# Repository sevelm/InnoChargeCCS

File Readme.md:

<!-- List of references -->
## Project References

### PyPLC
raspberry Pi based EVSE Controller https://github.com/uhi22/pyPLC

### EVerest
CPP Implementation of message structure https://github.com/EVerest/libiso15118
List of open charging management Repo https://github.com/EVerest

### SmartEVSE
Most promising software solution to read car SOC https://github.com/SmartEVSE/ESP32-PLC

### uhi22
Link of many ccs related project https://github.com/uhi22

### FOCCCI
Main reference for scheatic and hardware designs of QCA7005 https://github.com/uhi22/foccci

## Alternative Chips
`IS32CG5317` Seems an alternative for QCA7000

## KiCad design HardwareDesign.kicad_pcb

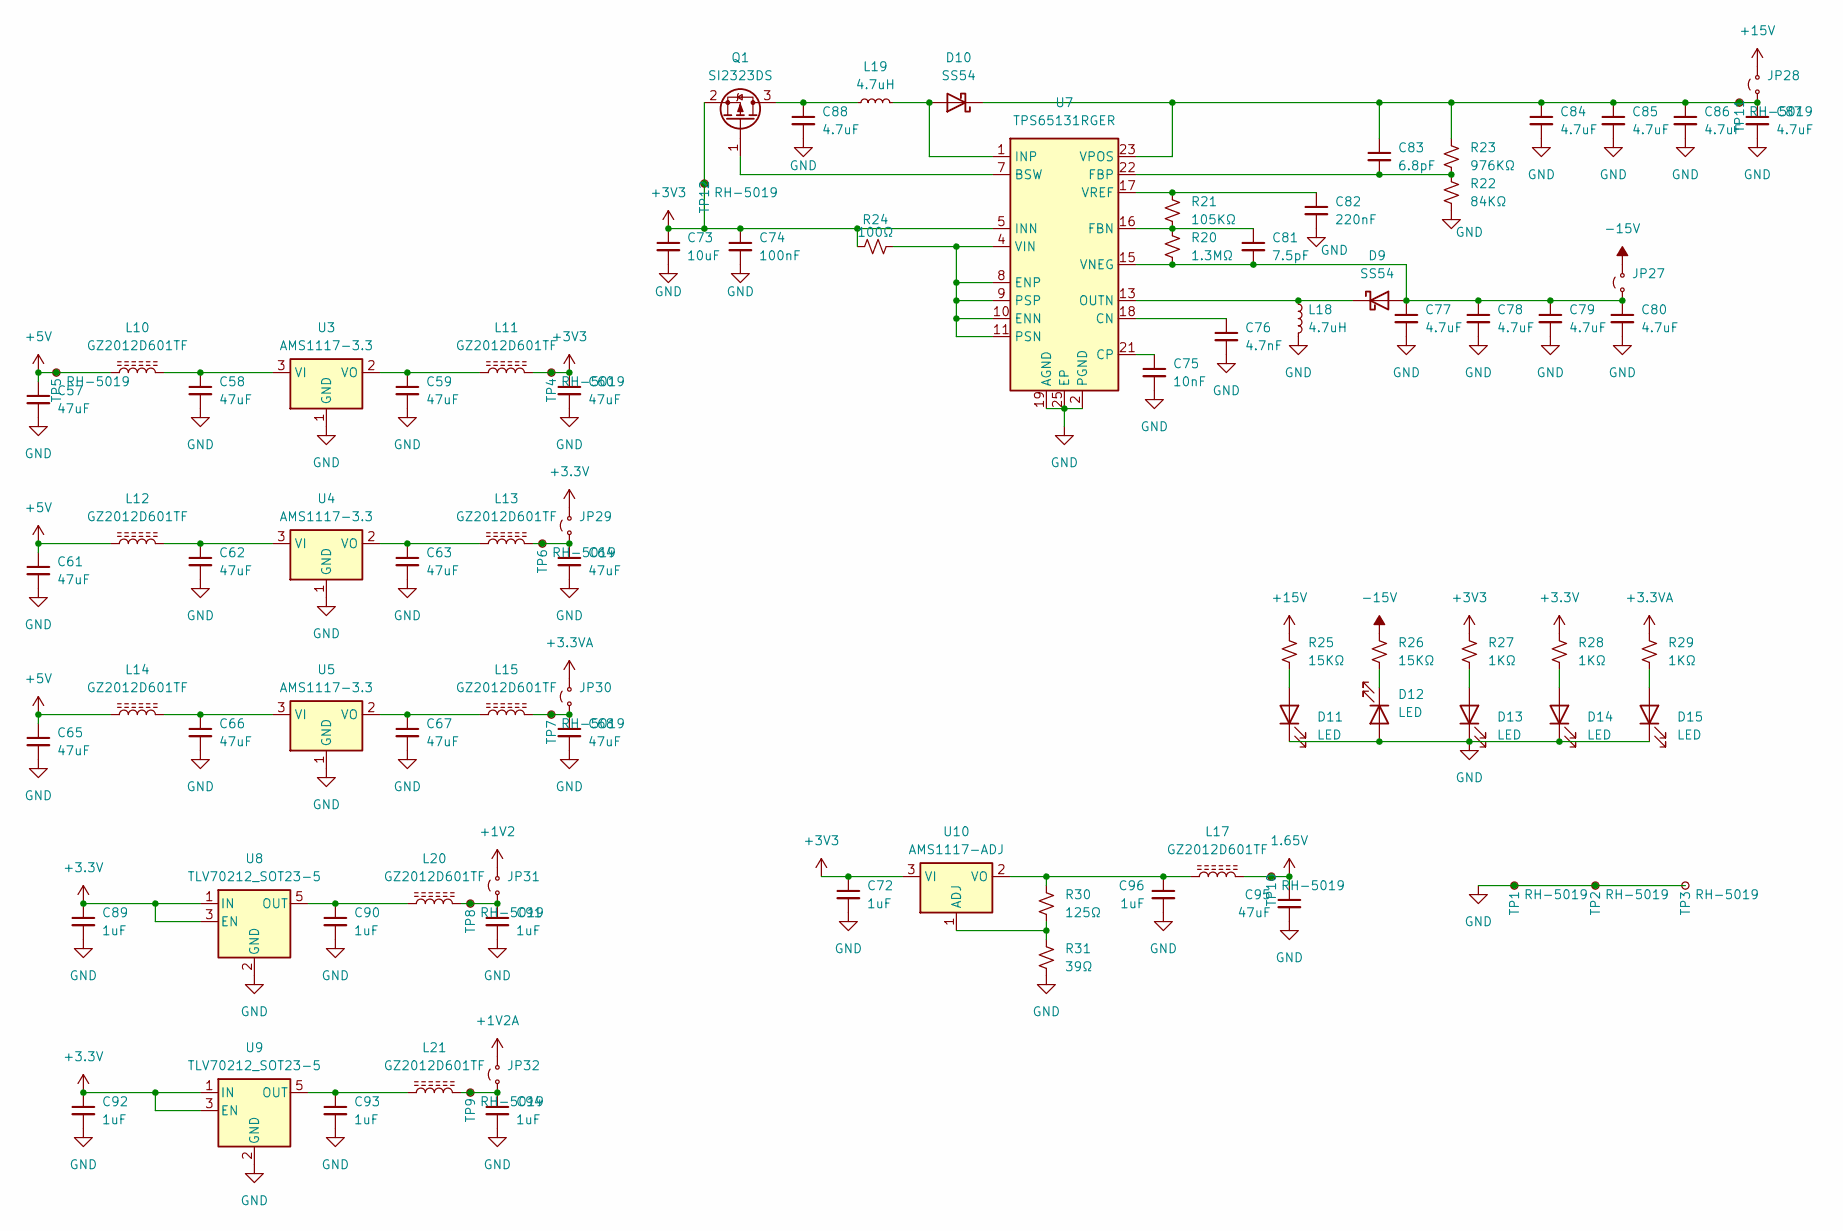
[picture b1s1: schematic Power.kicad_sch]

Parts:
C57, C58, C59, C60, C61, C62, C63, C64, C65, C66, C67, C68, C95: 47uF; C_0805_2012Metric; JLCPCB Part No # C16780
C72, C89, C90, C91, C92, C93, C94, C96: 1uF; C_0805_2012Metric; JLCPCB Part No # C28323
C73: 10uF; C_0805_2012Metric; JLCPCB Part No # C440198
C74: 100nF; C_0805_2012Metric; JLCPCB Part No # C28233
C75: 10nF; C_0805_2012Metric; JLCPCB Part No # C1710
C76: 4.7nF; C_0805_2012Metric; JLCPCB Part No # C1744
C77, C78, C79, C80, C84, C85, C86, C87, C88: 4.7uF; C_0805_2012Metric; JLCPCB Part No # C1779
C81: 7.5pF; C_0805_2012Metric; JLCPCB Part No # C519943
C82: 220nF; C_0805_2012Metric; JLCPCB Part No # C5378
C83: 6.8pF; C_0805_2012Metric; JLCPCB Part No # C1832
D9, D10: SS54; D_SMA; JLCPCB Part No # C7420369
D11, D12, D13, D14, D15: LED; LED_0805_2012Metric; JLCPCB Part No # C2297
JP27, JP28, JP29, JP30, JP31, JP32: SolderJumper-2_P1.3mm_Open_RoundedPad1.0x1.5mm
L10, L11, L12, L13, L14, L15, L17, L20, L21: GZ2012D601TF; L_0805_2012Metric; JLCPCB Part No # C1017
L18, L19: 4.7uH; L_Sunlord_SWPA3015S; JLCPCB Part No # C19398
Q1: SI2323DS; SOT-23-3; JLCPCB Part No # C5182044
R20: 1.3MΩ; R_0805_2012Metric; JLCPCB Part No # C413341
R21: 105KΩ; R_0805_2012Metric; JLCPCB Part No # C17410
R22: 84KΩ; R_0603_1608Metric; JLCPCB Part No # C706010
R23: 976KΩ; R_0805_2012Metric; JLCPCB Part No # C218737
R24: 100Ω; R_0805_2012Metric; JLCPCB Part No # C17408
R25, R26: 15KΩ; R_0805_2012Metric; JLCPCB Part No # C17475
R27, R28, R29: 1KΩ; R_0805_2012Metric; JLCPCB Part No # C17513
R30: 125Ω; R_0805_2012Metric; JLCPCB Part No # C3020059
R31: 39Ω; R_0805_2012Metric; JLCPCB Part No # C137534
TP1, TP2, TP3, TP4, TP5, TP6, TP7, TP8, TP9, TP10, TP11, TP12: RH-5019; TestPoint_Keystone_5019_Minature; JLCPCB Part No # C5199800
U3, U4, U5: AMS1117-3.3; SOT-223-3_TabPin2; JLCPCB Part No # C6186
U7: TPS65131RGER; VQFN-24-1EP_4x4mm_P0.5mm_EP2.45x2.45mm_ThermalVias; JLCPCB Part No # C87663
U8, U9: TLV70212_SOT23-5; SOT-23-5; JLCPCB Part No # C81462
U10: AMS1117-ADJ; SOT-223-3_TabPin2; JLCPCB Part No # C347224

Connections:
1.65V: C95.1, L17.1, TP10.1; also elsewhere on the board
+1V2: JP31.2 (B); also elsewhere on the board
+1V2A: JP32.2 (B); also elsewhere on the board
+3.3V: C89.1, C92.1, JP29.2 (B), R28.1, U8.1 (IN), U8.3 (EN), U9.1 (IN), U9.3 (EN); also elsewhere on the board
+3.3VA: JP30.2 (B), R29.1; also elsewhere on the board
+3V3: C60.1, C72.1, C73.1, C74.1, L11.2, Q1.2 (S), R24.1, R27.1, TP4.1, TP12.1, U7.5 (INN), U7.6 (INN), U10.3 (VI); also elsewhere on the board
+5V: C57.1, C61.1, C65.1, L10.1, L12.1, L14.1, TP5.1; also elsewhere on the board
+15V: JP28.2 (B), R25.1; also elsewhere on the board
-15V: JP27.2 (B), R26.1; also elsewhere on the board
GND: C57.2, C58.2, C59.2, C60.2, C61.2, C62.2, C63.2, C64.2, C65.2, C66.2, C67.2, C68.2, C72.2, C73.2, C74.2, C75.2, C76.2, C77.2, C78.2, C79.2, C80.2, C82.2, C84.2, C85.2, C86.2, C87.2, C88.2, C89.2, C90.2, C91.2, C92.2, C93.2, C94.2, C95.2, C96.2, D11.1 (K), D12.2 (A), D13.1 (K), D14.1 (K), D15.1 (K), L18.2, R22.2, R31.2, TP1.1, TP2.1, TP3.1, U3.1 (GND), U4.1 (GND), U5.1 (GND), U7.2 (PGND), U7.3 (PGND), U7.19 (AGND), U7.25 (EP), U8.2 (GND), U9.2 (GND); also elsewhere on the board
unnamed: C77.1, C78.1, C79.1, C80.1, C81.2, D9.2 (A), JP27.1 (A), R20.2, U7.15 (VNEG)
unnamed: D9.1 (K), L18.1, U7.13 (OUTN), U7.14 (OUTN)
unnamed: D10.2 (A), L19.2, U7.1 (INP), U7.24 (INP)
unnamed: C83.1, C84.1, C85.1, C86.1, C87.1, D10.1 (K), JP28.1 (A), R23.1, TP11.1, U7.23 (VPOS)
unnamed: D11.2 (A), R25.2
unnamed: D12.1 (K), R26.2
unnamed: D13.2 (A), R27.2
unnamed: D14.2 (A), R28.2
unnamed: D15.2 (A), R29.2
unnamed: C64.1, JP29.1 (A), L13.2, TP6.1
unnamed: C68.1, JP30.1 (A), L15.2, TP7.1
unnamed: C91.1, JP31.1 (A), L20.2, TP8.1
unnamed: C94.1, JP32.1 (A), L21.2, TP9.1
unnamed: C88.1, L19.1, Q1.3 (D)
unnamed: Q1.1 (G), U7.7 (BSW)
unnamed: C58.1, L10.2, U3.3 (VI)
unnamed: C59.1, L11.1, U3.2 (VO)
unnamed: C62.1, L12.2, U4.3 (VI)
unnamed: C63.1, L13.1, U4.2 (VO)
unnamed: C66.1, L14.2, U5.3 (VI)
unnamed: C67.1, L15.1, U5.2 (VO)
unnamed: C76.1, U7.18 (CN)
unnamed: C75.1, U7.21 (CP)
unnamed: R24.2, U7.4 (VIN), U7.8 (ENP), U7.9 (PSP), U7.10 (ENN), U7.11 (PSN)
unnamed: C81.1, R20.1, R21.2, U7.16 (FBN)
unnamed: C83.2, R22.1, R23.2, U7.22 (FBP)
unnamed: C82.1, R21.1, U7.17 (VREF)
unnamed: C90.1, L20.1, U8.5 (OUT)
unnamed: C93.1, L21.1, U9.5 (OUT)
unnamed: R30.2, R31.1, U10.1 (ADJ)
unnamed: C96.1, L17.2, R30.1, U10.2 (VO)

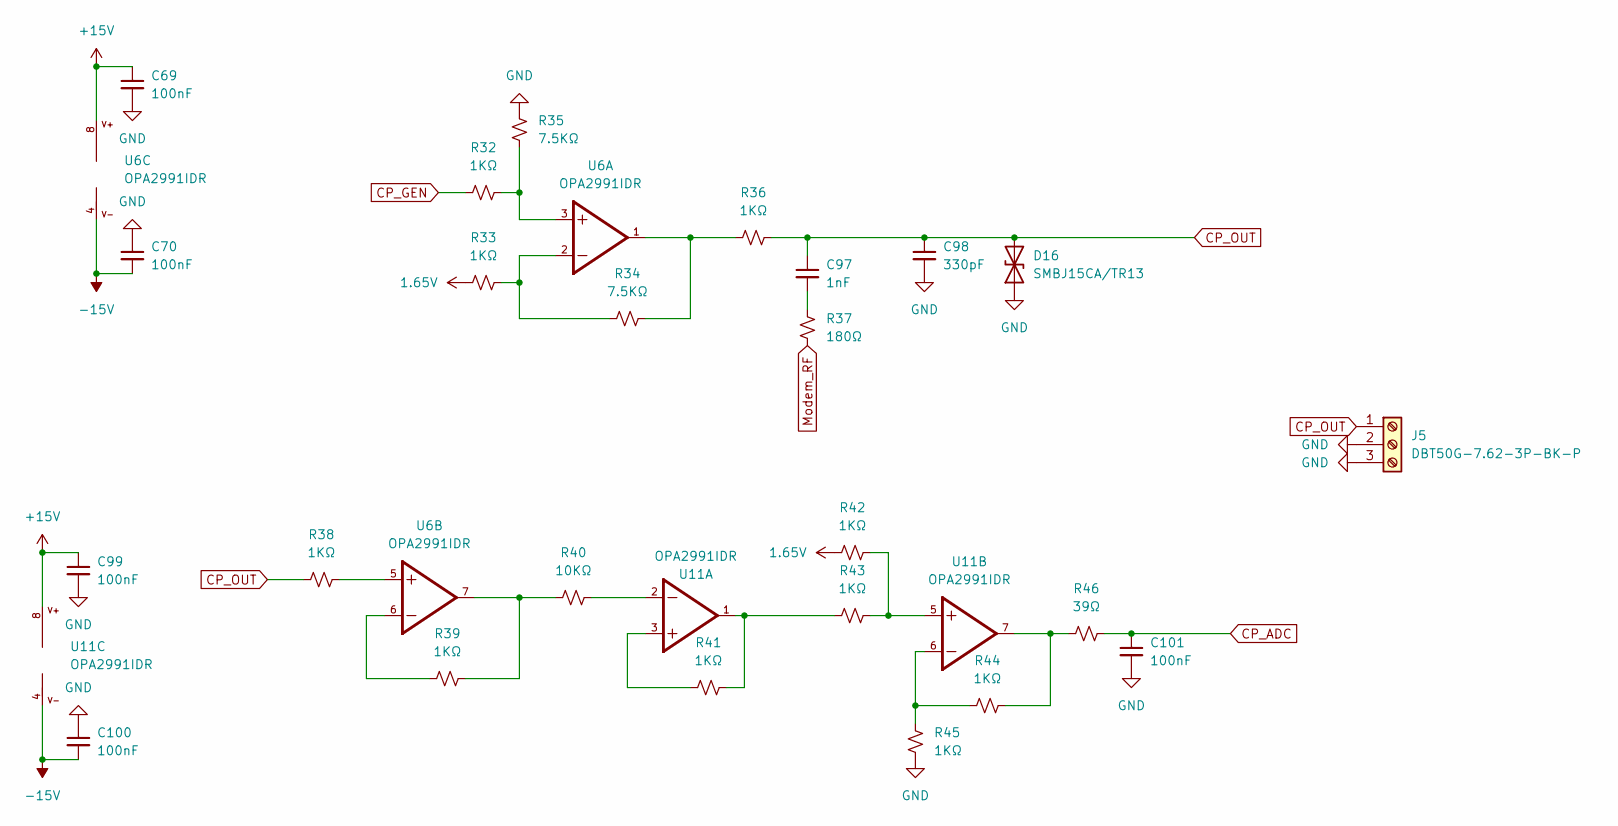
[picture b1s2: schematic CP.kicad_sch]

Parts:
C69, C70, C99, C100, C101: 100nF; C_0805_2012Metric; JLCPCB Part No # C28233
C97: 1nF; C_0805_2012Metric; JLCPCB Part No # C46653
C98: 330pF; C_0805_2012Metric; JLCPCB Part No # C1815
D16: SMBJ15CA/TR13; D_SMB; JLCPCB Part No # C78410
J5: DBT50G-7.62-3P-BK-P; PhoenixContact_GMSTBVA_2,5_3-G-7,62_1x03_P7.62mm_Vertical; JLCPCB Part No # C496128
R32, R33, R36, R38, R39, R41, R42, R43, R44, R45: 1KΩ; R_0805_2012Metric; JLCPCB Part No # C17513
R34, R35: 7.5KΩ; R_0805_2012Metric; JLCPCB Part No # C17807
R37: 180Ω; R_0805_2012Metric; JLCPCB Part No # C25270
R40: 10KΩ; R_0805_2012Metric; JLCPCB Part No # C17414
R46: 39Ω; R_0805_2012Metric; JLCPCB Part No # C137534
U6, U11: OPA2991IDR; SOIC-8_3.9x4.9mm_P1.27mm; MOUSER_PART_NUMBER 595-OPA2991IPWR

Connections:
1.65V: R33.2, R42.2; also elsewhere on the board
+15V: C69.1, C99.1, U6.8, U11.8; also elsewhere on the board
-15V: C70.2, C100.2, U6.4, U11.4; also elsewhere on the board
CP_ADC: C101.1, R46.1; also elsewhere on the board
CP_GEN: R32.1; also elsewhere on the board
CP_OUT: C97.1, C98.1, D16.2 (A2), J5.1, R36.1, R38.2
GND: C69.2, C70.1, C98.2, C99.2, C100.1, C101.2, D16.1 (A1), J5.2, J5.3, R35.1, R45.2; also elsewhere on the board
Modem_RF: R37.2; also elsewhere on the board
unnamed: C97.2, R37.1
unnamed: R32.2, R35.2, U6.3
unnamed: R33.1, R34.2, U6.2
unnamed: R34.1, R36.2, U6.1
unnamed: R38.1, U6.5
unnamed: R39.1, R40.1, U6.7
unnamed: R39.2, U6.6
unnamed: R40.2, U11.2
unnamed: R41.1, R43.2, U11.1
unnamed: R41.2, U11.3
unnamed: R42.1, R43.1, U11.5
unnamed: R44.1, R46.2, U11.7
unnamed: R44.2, R45.1, U11.6

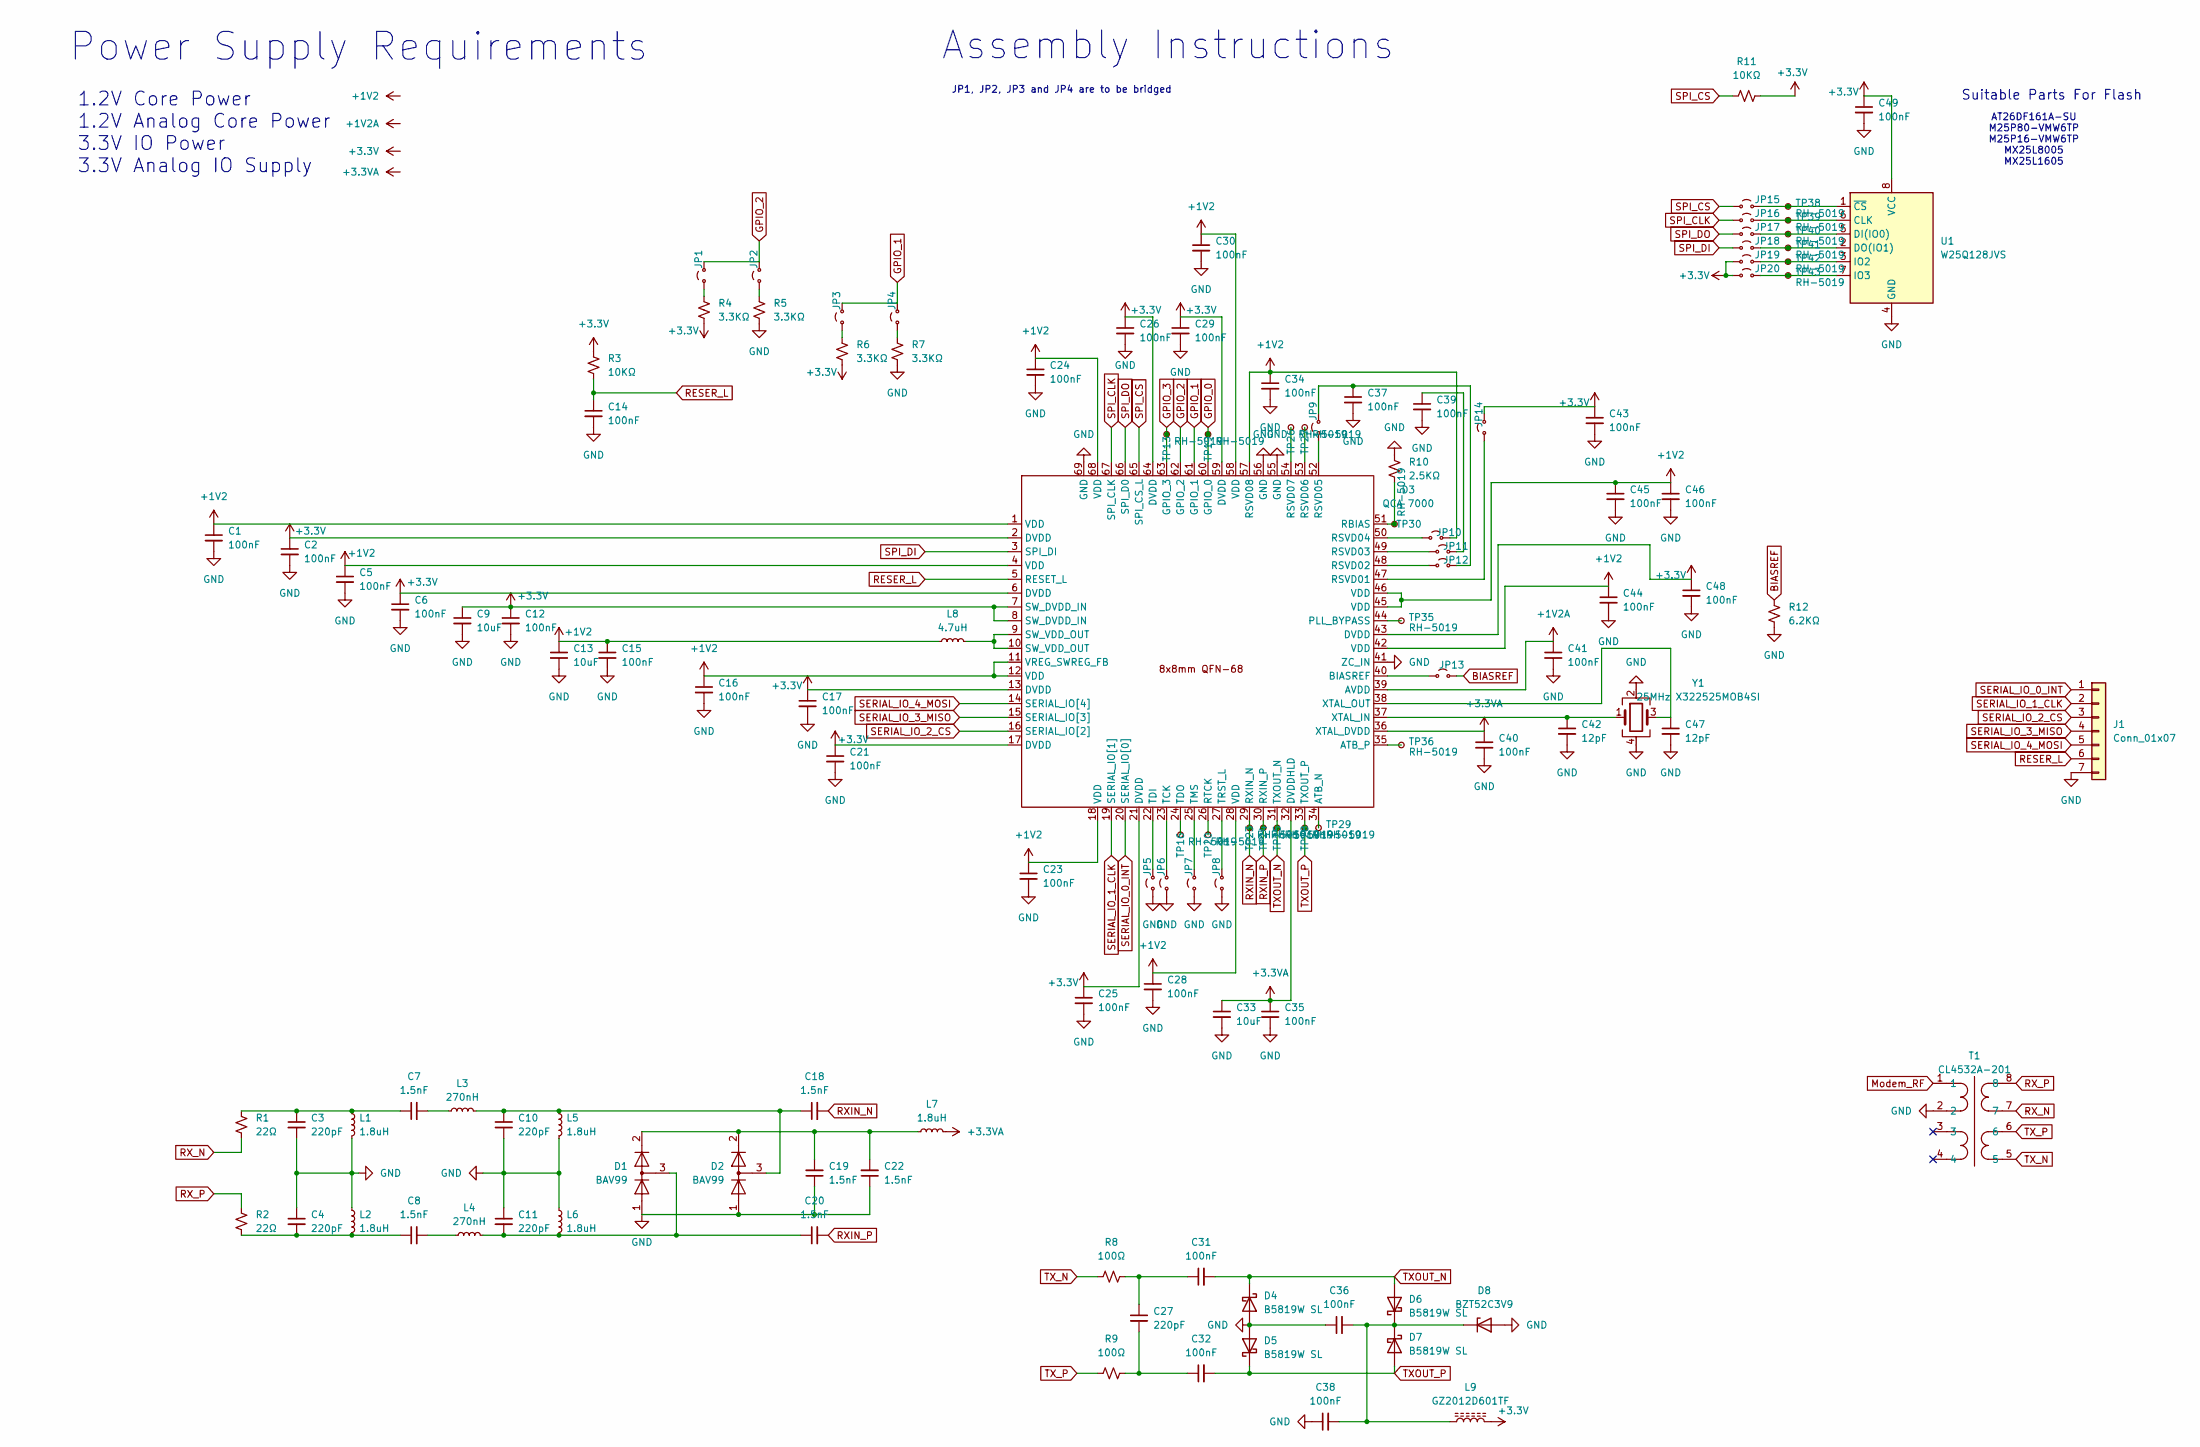
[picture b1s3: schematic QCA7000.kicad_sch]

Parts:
C1, C2, C5, C6, C12, C14, C15, C16, C17, C21, C23, C24, C25, C26, C28, C29, C30, C31, C32, C34, C35, C36, C37, C38, C39, C40, C41, C43, C44, C45, C46, C48, C49: 100nF; C_0805_2012Metric; JLCPCB Part No # C28233
C3, C4, C10, C11, C27: 220pF; C_0805_2012Metric; JLCPCB Part No # C107145
C7, C8, C18, C19, C20, C22: 1.5nF; C_0805_2012Metric; JLCPCB Part No # C107142
C9, C13, C33: 10uF; C_0805_2012Metric; JLCPCB Part No # C440198
C42, C47: 12pF; C_0805_2012Metric; JLCPCB Part No # C1792
D1, D2: BAV99; SOT-23; JLCPCB Part No # C7420336
D3: QCA 7000; QFN-68-1EP_8x8mm_P0.4mm_EP5.2x5.2mm_ThermalVias
D4, D5, D6, D7: B5819W SL; D_SOD-123; JLCPCB Part No # C8598
D8: BZT52C3V9; D_SOD-123; JLCPCB Part No # C726992
J1: Conn_01x07; PinHeader_1x07_P2.54mm_Vertical
JP1, JP2, JP3, JP4, JP5, JP6, JP7, JP8, JP9, JP10, JP11, JP12, JP13, JP14, JP15, JP16, JP17, JP18, JP19, JP20: SolderJumper-2_P1.3mm_Open_RoundedPad1.0x1.5mm
L1, L2, L5, L6, L7: 1.8uH; L_0805_2012Metric; JLCPCB Part No # C479897
L3, L4: 270nH; L_0805_2012Metric; JLCPCB Part No # C404430
L8: 4.7uH; L_Sunlord_SWPA3015S; JLCPCB Part No # C19398
L9: GZ2012D601TF; L_0805_2012Metric; JLCPCB Part No # C1017
R1, R2: 22Ω; R_0805_2012Metric; JLCPCB Part No # C17561
R3, R11: 10KΩ; R_0805_2012Metric; JLCPCB Part No # C17414
R4, R5, R6, R7: 3.3KΩ; R_0805_2012Metric; JLCPCB Part No # C26010
R8, R9: 100Ω; R_0805_2012Metric; JLCPCB Part No # C17408
R10: 2.5KΩ; R_0805_2012Metric; JLCPCB Part No # C5713447
R12: 6.2KΩ; R_0805_2012Metric; JLCPCB Part No # C17767
T1: CL4532A-201; transformerCL4532A-201; JLCPCB Part No # C2904734
TP13, TP16, TP19, TP20, TP23, TP24, TP25, TP26, TP27, TP28, TP29, TP30, TP35, TP36, TP38, TP39, TP40, TP41, TP42, TP43: RH-5019; TestPoint_Keystone_5019_Minature; JLCPCB Part No # C5199800
U1: W25Q128JVS; SOIC-8_5.23x5.23mm_P1.27mm; JLCPCB Part No # C113767
Y1: 25MHz X322525MOB4SI; Crystal_SMD_3225-4Pin_3.2x2.5mm; JLCPCB Part No # C9006

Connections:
+1V2: C1.1, C5.1, C13.1, C15.1, C16.1, C23.1, C24.1, C28.1, C30.1, C34.1, C44.1, C45.1, C46.1, D3.1 (VDD), D3.4 (VDD), D3.11 (VREG_SWREG_FB), D3.12 (VDD), D3.18 (VDD), D3.28 (VDD), D3.42 (VDD), D3.45 (VDD), D3.46 (VDD), D3.57 (RSVD08), D3.58 (VDD), D3.68 (VDD), JP10.2 (B), L8.1; also elsewhere on the board
+1V2A: C41.1, D3.39 (AVDD); also elsewhere on the board
+3.3V: C2.1, C6.1, C9.1, C12.1, C17.1, C21.1, C25.1, C26.1, C29.1, C43.1, C48.1, C49.1, D3.2 (DVDD), D3.6 (DVDD), D3.7 (SW_DVDD_IN), D3.8 (SW_DVDD_IN), D3.13 (DVDD), D3.17 (DVDD), D3.21 (DVDD), D3.43 (DVDD), D3.59 (DVDD), D3.64 (DVDD), JP14.2 (B), JP19.1 (A), JP20.1 (A), L9.2, R3.1, R4.2, R6.2, R11.2, U1.8 (VCC); also elsewhere on the board
+3.3VA: C33.1, C35.1, C40.1, D3.32 (DVDDHLD), D3.36 (XTAL_DVDD), L7.2; also elsewhere on the board
BIASREF: JP13.2 (B), R12.1
GND: C1.2, C2.2, C3.2, C4.1, C5.2, C6.2, C9.2, C10.2, C11.1, C12.2, C13.2, C14.2, C15.2, C16.2, C17.2, C19.1, C21.2, C22.1, C23.2, C24.2, C25.2, C26.2, C28.2, C29.2, C30.2, C33.2, C34.2, C35.2, C36.1, C37.2, C38.1, C39.2, C40.2, C41.2, C42.2, C43.2, C44.2, C45.2, C46.2, C47.2, C48.2, C49.2, D1.1 (K), D2.1 (K), D3.41 (ZC_IN), D3.55 (GND), D3.56 (GND), D3.69 (GND), D4.2 (A), D5.2 (A), D8.2 (A), J1.7, JP5.1 (A), JP6.1 (A), JP7.1 (A), JP8.1 (A), L1.2, L2.1, L5.2, L6.1, R5.2, R7.2, R10.1, R12.2, T1.2, U1.4 (GND), Y1.2, Y1.4; also elsewhere on the board
GPIO_0: D3.60 (GPIO_0), TP19.1
GPIO_1: D3.61 (GPIO_1), JP3.2 (B), JP4.2 (B)
GPIO_2: D3.62 (GPIO_2), JP1.2 (B), JP2.2 (B)
GPIO_3: D3.63 (GPIO_3), TP13.1
Modem_RF: T1.1; also elsewhere on the board
unnamed: C3.1, C7.1, L1.1, R1.1
unnamed: C4.2, C8.1, L2.2, R2.2
unnamed: C7.2, L3.1
unnamed: C8.2, L4.1
unnamed: C10.1, C18.1, D2.3 (K), L3.2, L5.1
unnamed: C11.2, C20.1, D1.3 (K), L4.2, L6.2
unnamed: C27.1, C31.1, R8.2
unnamed: C27.2, C32.1, R9.2
unnamed: C19.2, C22.2, D1.2 (A), D2.2 (A), L7.1
unnamed: D3.34 (ATB_N), TP29.1
unnamed: D3.35 (ATB_P), TP36.1
unnamed: D3.40 (BIASREF), JP13.1 (A)
unnamed: D3.44 (PLL_BYPASS), TP35.1
unnamed: D3.51 (RBIAS), R10.2, TP30.1
unnamed: D3.47 (RSVD01), JP14.1 (A)
unnamed: D3.48 (RSVD02), JP12.1 (A)
unnamed: D3.49 (RSVD03), JP11.1 (A)
unnamed: D3.50 (RSVD04), JP10.1 (A)
unnamed: D3.52 (RSVD05), JP9.1 (A)
unnamed: D3.53 (RSVD06), TP27.1
unnamed: D3.54 (RSVD07), TP26.1
unnamed: D3.26 (RTCK), TP20.1
unnamed: D3.9 (SW_VDD_OUT), D3.10 (SW_VDD_OUT), L8.2
unnamed: D3.23 (TCK), JP6.2 (B)
unnamed: D3.22 (TDI), JP5.2 (B)
unnamed: D3.24 (TDO), TP16.1
unnamed: D3.25 (TMS), JP7.2 (B)
unnamed: D3.27 (TRST_L), JP8.2 (B)
unnamed: C42.1, D3.37 (XTAL_IN), Y1.1
unnamed: C47.1, D3.38 (XTAL_OUT), Y1.3
unnamed: C36.2, C38.2, D6.1 (K), D7.1 (K), D8.1 (K), L9.1
unnamed: JP1.1 (A), R4.1
unnamed: JP2.1 (A), R5.1
unnamed: JP3.1 (A), R6.1
unnamed: JP4.1 (A), R7.1
unnamed: C39.1, JP11.2 (B)
unnamed: C37.1, JP9.2 (B), JP12.2 (B)
unnamed: JP15.2 (B), TP38.1, U1.1 (~CS)
unnamed: JP16.2 (B), TP39.1, U1.6 (CLK)
unnamed: JP17.2 (B), TP40.1, U1.5 (DI(IO0))
unnamed: JP18.2 (B), TP41.1, U1.2 (DO(IO1))
unnamed: JP19.2 (B), TP42.1, U1.3 (IO2)
unnamed: JP20.2 (B), TP43.1, U1.7 (IO3)
RESER_L: C14.1, D3.5 (RESET_L), J1.6, R3.2; also elsewhere on the board
RXIN_N: C18.2, D3.29 (RXIN_N), TP23.1
RXIN_P: C20.2, D3.30 (RXIN_P), TP24.1
RX_N: R1.2, T1.7
RX_P: R2.1, T1.8
SERIAL_IO_0_INT: D3.20 (SERIAL_IO[0]), J1.1; also elsewhere on the board
SERIAL_IO_1_CLK: D3.19 (SERIAL_IO[1]), J1.2; also elsewhere on the board
SERIAL_IO_2_CS: D3.16 (SERIAL_IO[2]), J1.3; also elsewhere on the board
SERIAL_IO_3_MISO: D3.15 (SERIAL_IO[3]), J1.4; also elsewhere on the board
SERIAL_IO_4_MOSI: D3.14 (SERIAL_IO[4]), J1.5; also elsewhere on the board
SPI_CLK: D3.67 (SPI_CLK), JP16.1 (A)
SPI_CS: D3.65 (SPI_CS_L), JP15.1 (A), R11.1
SPI_DI: D3.3 (SPI_DI), JP18.1 (A)
SPI_DO: D3.66 (SPI_D0), JP17.1 (A)
TXOUT_N: C31.2, D3.31 (TXOUT_N), D4.1 (K), D6.2 (A), TP25.1
TXOUT_P: C32.2, D3.33 (TXOUT_P), D5.1 (K), D7.2 (A), TP28.1
TX_N: R8.1, T1.5
TX_P: R9.1, T1.6

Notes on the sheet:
Power Supply Requirements
AT26DF161A-SU M25P80-VMW6TP M25P16-VMW6TP MX25L8005 MX25L1605
JP1, JP2, JP3 and JP4 are to be bridged
Suitable Parts For Flash
1.2V Core Power 1.2V Analog Core Power 3.3V IO Power 3.3V Analog IO Supply
Assembly Instructions

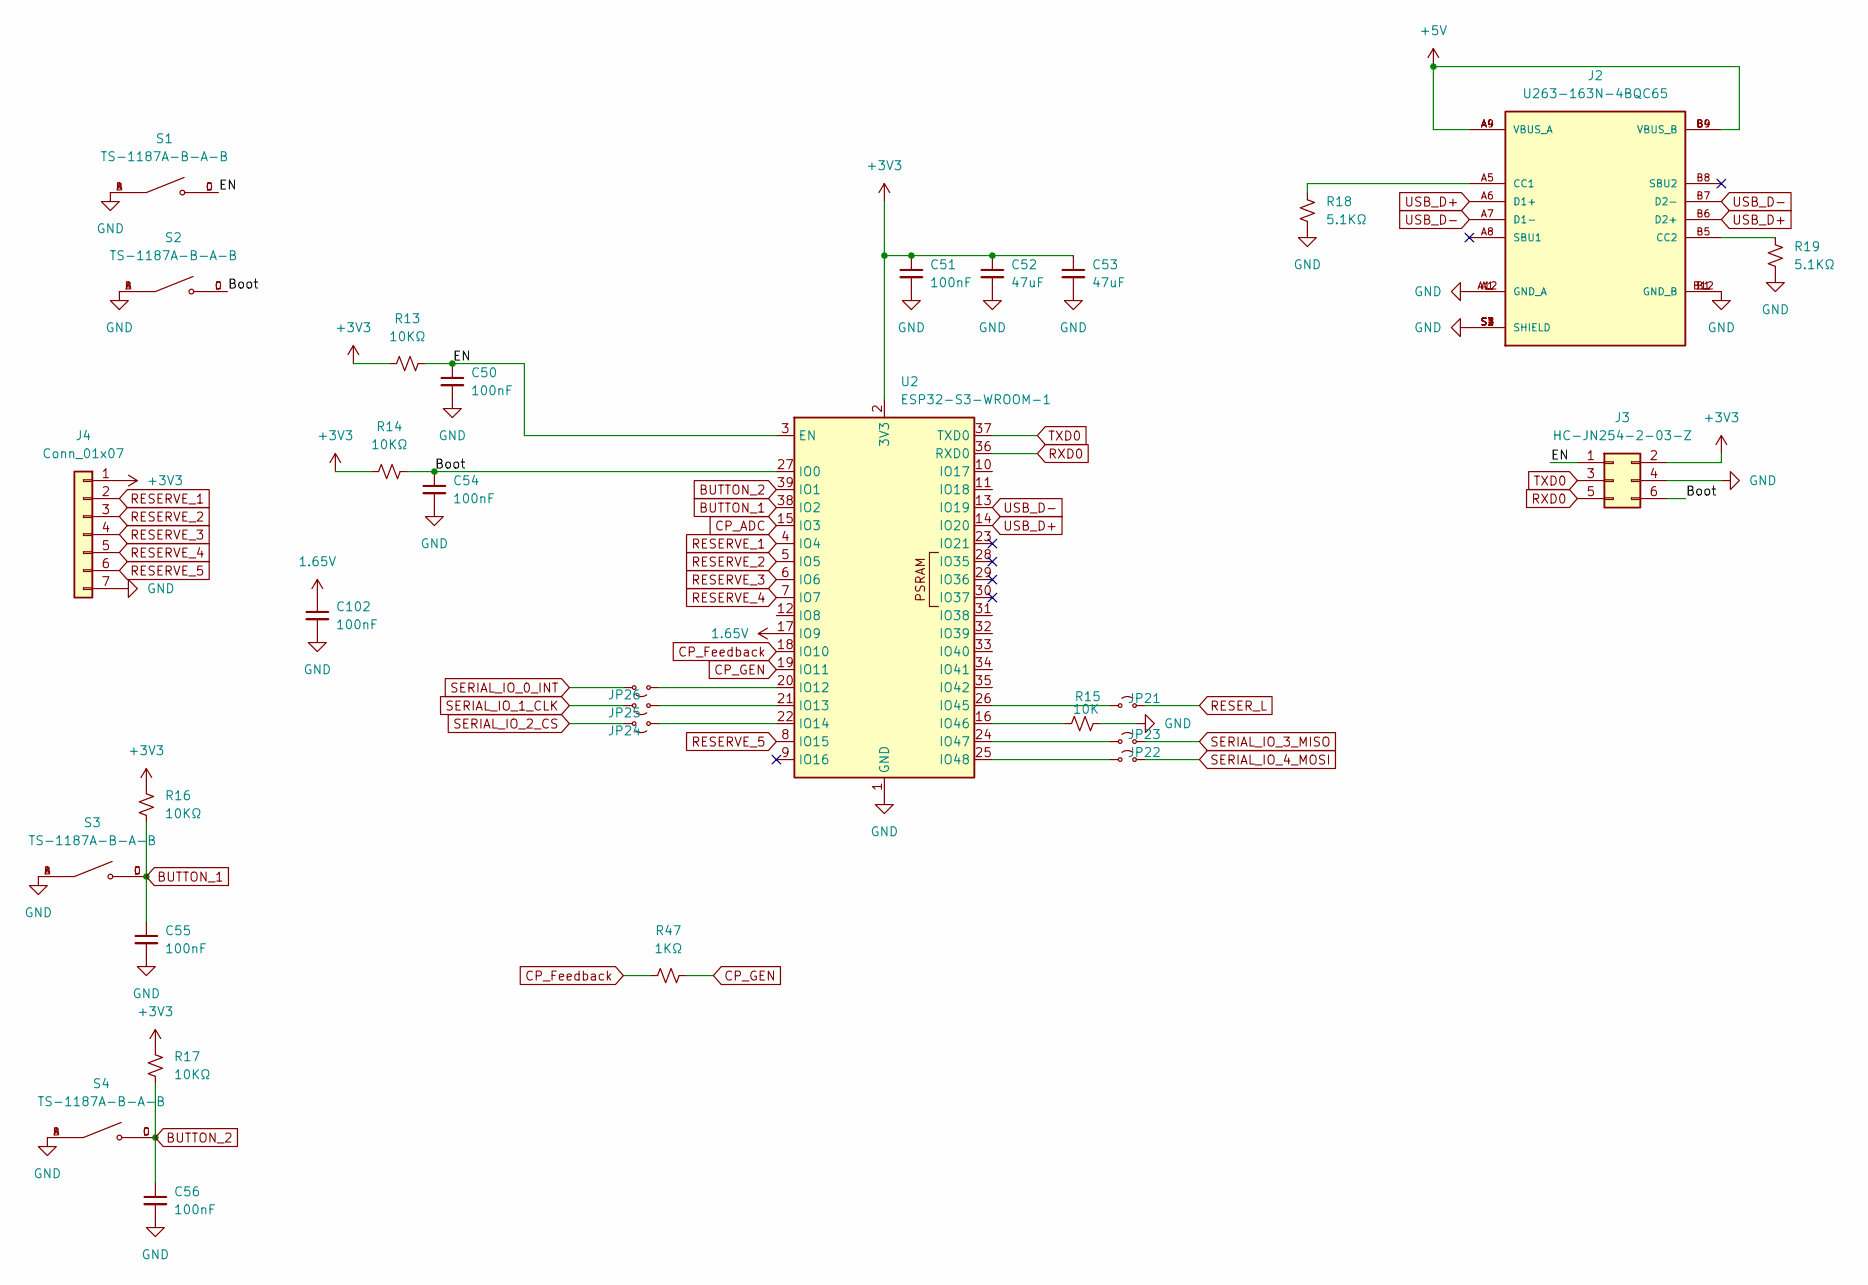
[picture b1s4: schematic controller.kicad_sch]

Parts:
C50, C51, C54, C55, C56, C102: 100nF; C_0805_2012Metric; JLCPCB Part No # C28233
C52, C53: 47uF; C_0805_2012Metric; JLCPCB Part No # C16780
J2: U263-163N-4BQC65; GCT_USB4120-03-C_REVA; PARTREV A; JLCPCB Part No # C2938598
J3: HC-JN254-2-03-Z; IDC-Header_2x03_P2.54mm_Vertical; JLCPCB Part No # C5372863
J4: Conn_01x07; PinHeader_1x07_P2.54mm_Vertical
JP21, JP22, JP23, JP24, JP25, JP26: SolderJumper-2_P1.3mm_Open_RoundedPad1.0x1.5mm
R13, R14, R16, R17: 10KΩ; R_0805_2012Metric; JLCPCB Part No # C17414
R15: 10K; R_0805_2012Metric; JLCPCB Part No # C17414
R18, R19: 5.1KΩ; R_0805_2012Metric; JLCPCB Part No # C27834
R47: 1KΩ; R_0805_2012Metric; JLCPCB Part No # C17513
S1, S2, S3, S4: TS-1187A-B-A-B; SW_TS-1187A-B-A-B; PARTREV A0; JLCPCB Part No # C318884
U2: ESP32-S3-WROOM-1; JLCPCB Part No # C2913202

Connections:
1.65V: C102.1, U2.17 (IO9); also elsewhere on the board
+3V3: C51.1, C52.1, C53.1, J3.2, J4.1, R13.1, R14.1, R16.2, R17.2, U2.2 (3V3); also elsewhere on the board
+5V: J2.A4 (VBUS_A), J2.A9 (VBUS_A), J2.B4 (VBUS_B), J2.B9 (VBUS_B); also elsewhere on the board
/ESP32/Boot: C54.1, J3.6, R14.2, S2.C, S2.D, U2.27 (IO0)
/ESP32/EN: C50.1, J3.1, R13.2, S1.C, S1.D, U2.3 (EN)
BUTTON_1: C55.1, R16.1, S3.C, S3.D, U2.38 (IO2)
BUTTON_2: C56.1, R17.1, S4.C, S4.D, U2.39 (IO1)
CP_ADC: U2.15 (IO3); also elsewhere on the board
CP_Feedback: R47.1, U2.18 (IO10)
CP_GEN: R47.2, U2.19 (IO11); also elsewhere on the board
GND: C50.2, C51.2, C52.2, C53.2, C54.2, C55.2, C56.2, C102.2, J2.A1 (GND_A), J2.A12 (GND_A), J2.B1 (GND_B), J2.B12 (GND_B), J2.S1 (SHIELD), J2.S2 (SHIELD), J2.S3 (SHIELD), J2.S4 (SHIELD), J3.4, J4.7, R15.2, R18.1, R19.1, S1.A, S1.B, S2.A, S2.B, S3.A, S3.B, S4.A, S4.B, U2.1 (GND), U2.40 (GND), U2.41 (GND); also elsewhere on the board
unnamed: J2.A5 (CC1), R18.2
unnamed: J2.B5 (CC2), R19.2
unnamed: JP21.1 (A), U2.26 (IO45)
unnamed: JP22.1 (A), U2.25 (IO48)
unnamed: JP23.1 (A), U2.24 (IO47)
unnamed: JP24.1 (A), U2.22 (IO14)
unnamed: JP25.1 (A), U2.21 (IO13)
unnamed: JP26.1 (A), U2.20 (IO12)
unnamed: R15.1, U2.16 (IO46)
RESERVE_1: J4.2, U2.4 (IO4)
RESERVE_2: J4.3, U2.5 (IO5)
RESERVE_3: J4.4, U2.6 (IO6)
RESERVE_4: J4.5, U2.7 (IO7)
RESERVE_5: J4.6, U2.8 (IO15)
RESER_L: JP21.2 (B); also elsewhere on the board
RXD0: J3.5, U2.36 (RXD0)
SERIAL_IO_0_INT: JP26.2 (B); also elsewhere on the board
SERIAL_IO_1_CLK: JP25.2 (B); also elsewhere on the board
SERIAL_IO_2_CS: JP24.2 (B); also elsewhere on the board
SERIAL_IO_3_MISO: JP23.2 (B); also elsewhere on the board
SERIAL_IO_4_MOSI: JP22.2 (B); also elsewhere on the board
TXD0: J3.3, U2.37 (TXD0)
USB_D+: J2.A6 (D1+), J2.B6 (D2+), U2.14 (IO20)
USB_D-: J2.A7 (D1-), J2.B7 (D2-), U2.13 (IO19)
